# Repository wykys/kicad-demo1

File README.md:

# kicad-demo1
KiCAD demo1 project

[RS-12-L](https://www.tme.eu/en/Document/c23d5af46047cd50f4ab84101c968917/rs.pdf)

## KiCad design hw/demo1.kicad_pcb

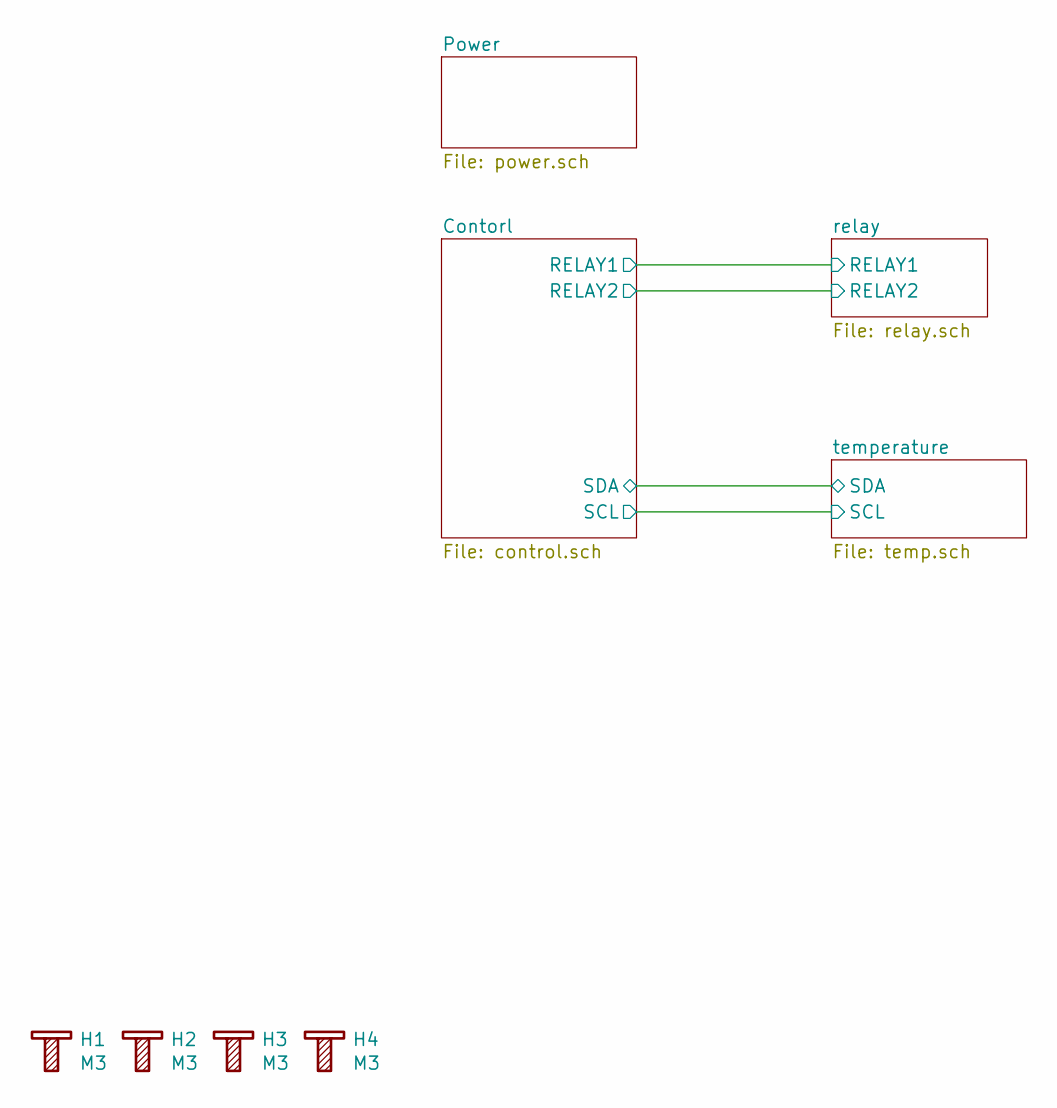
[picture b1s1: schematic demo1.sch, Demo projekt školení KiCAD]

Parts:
H1, H2, H3, H4: M3; Bolt_M3

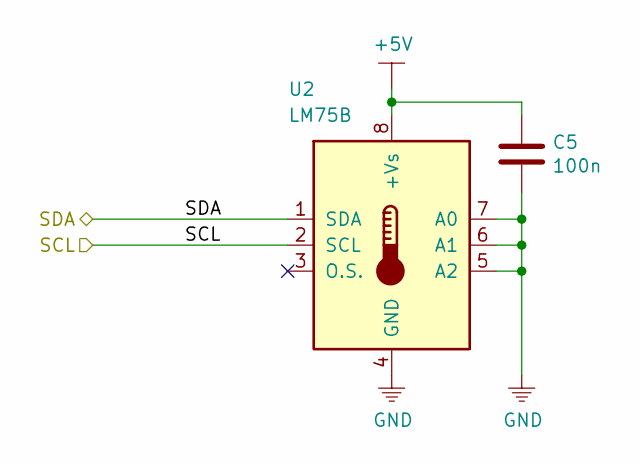
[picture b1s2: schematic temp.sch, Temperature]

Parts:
C5: 100n; C_0805_2012Metric
U2: LM75B; SOIC-8_3.9x4.9mm_P1.27mm

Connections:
+5V: C5.1, U2.8 (+Vs); also elsewhere on the board
/Contorl/SCL: U2.2 (SCL); also elsewhere on the board
/Contorl/SDA: U2.1 (SDA); also elsewhere on the board
GND: C5.2, U2.4 (GND), U2.5 (A2), U2.6 (A1), U2.7 (A0); also elsewhere on the board

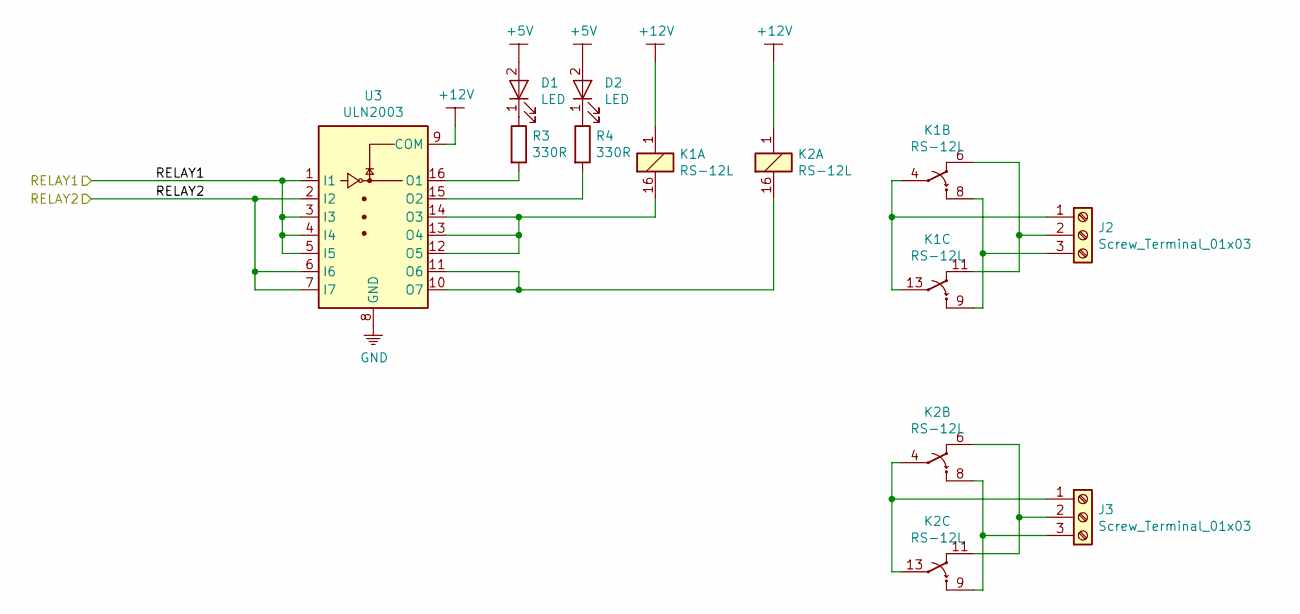
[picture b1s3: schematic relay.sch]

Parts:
D1, D2: LED; LED_0805_2012Metric
J2, J3: Screw_Terminal_01x03; PhoenixContact_MC_1,5_3-G-3.5_1x03_P3.50mm_Horizontal
K1, K2: RS-12L; RS-12-L
R3, R4: 330R; R_0805_2012Metric
U3: ULN2003; SOIC-16_3.9x9.9mm_P1.27mm

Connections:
+5V: D1.2 (A), D2.2 (A); also elsewhere on the board
+12V: K1.1, K2.1, U3.9 (COM); also elsewhere on the board
/Contorl/RELAY1: U3.1 (I1), U3.3 (I3), U3.4 (I4), U3.5 (I5); also elsewhere on the board
/Contorl/RELAY2: U3.2 (I2), U3.6 (I6), U3.7 (I7); also elsewhere on the board
GND: U3.8 (GND); also elsewhere on the board
unnamed: D1.1 (K), R3.1
unnamed: D2.1 (K), R4.1
unnamed: J2.1, K1.4, K1.13
unnamed: J2.2, K1.6, K1.11
unnamed: J2.3, K1.8, K1.9
unnamed: J3.1, K2.4, K2.13
unnamed: J3.2, K2.6, K2.11
unnamed: J3.3, K2.8, K2.9
unnamed: K1.16, U3.12 (O5), U3.13 (O4), U3.14 (O3)
unnamed: K2.16, U3.10 (O7), U3.11 (O6)
unnamed: R3.2, U3.16 (O1)
unnamed: R4.2, U3.15 (O2)

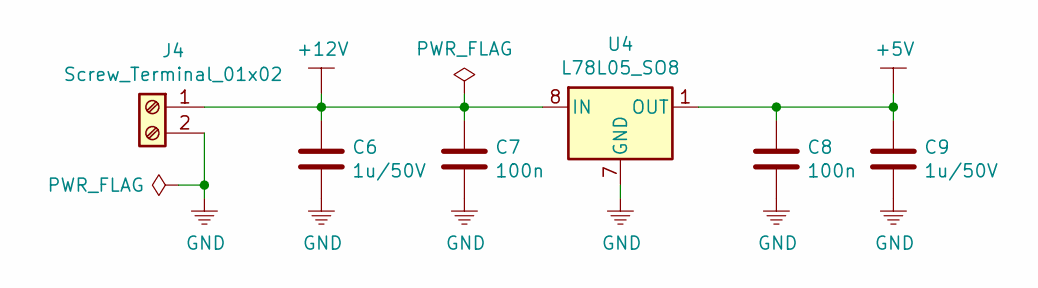
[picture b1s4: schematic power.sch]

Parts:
C6, C9: 1u/50V; C_0805_2012Metric
C7, C8: 100n; C_0805_2012Metric
J4: Screw_Terminal_01x02; PhoenixContact_MC_1,5_2-G-3.5_1x02_P3.50mm_Horizontal
U4: L78L05_SO8; SOIC-8_3.9x4.9mm_P1.27mm

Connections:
+5V: C8.1, C9.1, U4.1 (OUT); also elsewhere on the board
+12V: C6.1, C7.1, J4.1, U4.8 (IN); also elsewhere on the board
GND: C6.2, C7.2, C8.2, C9.2, J4.2, U4.2 (GND), U4.3 (GND), U4.6 (GND), U4.7 (GND); also elsewhere on the board

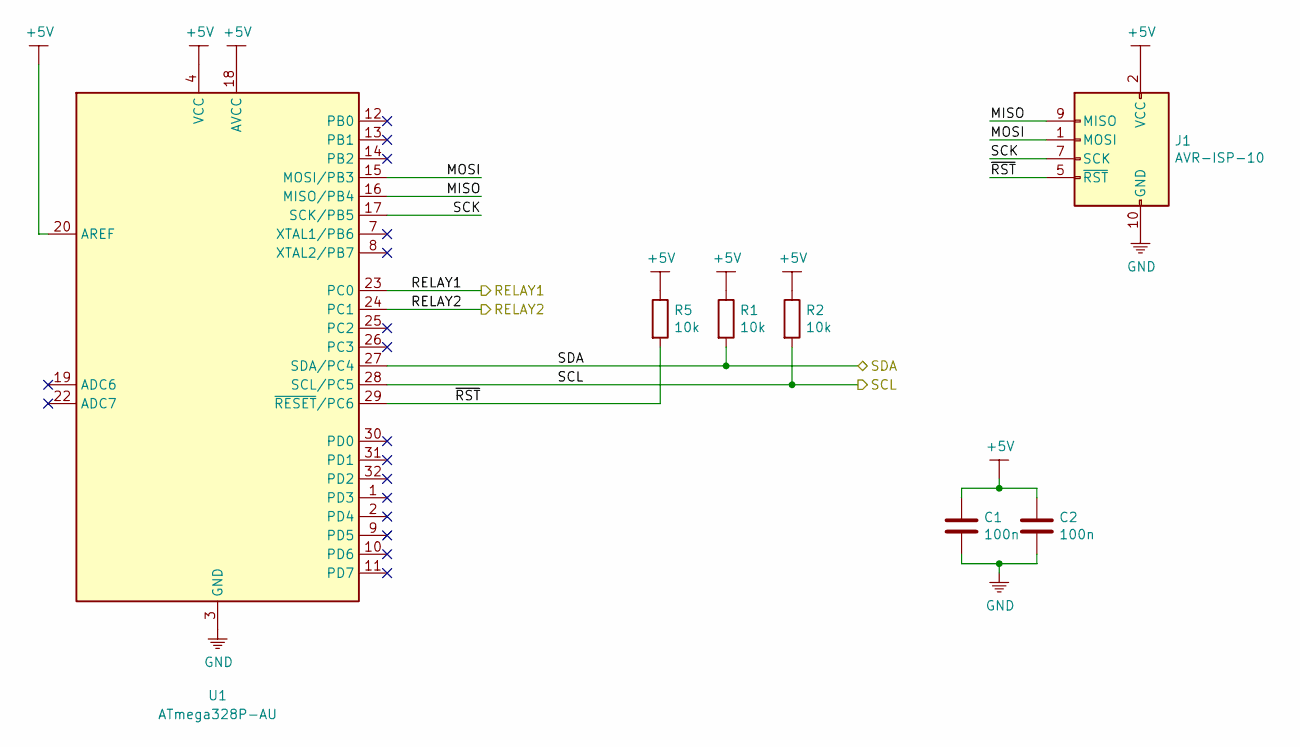
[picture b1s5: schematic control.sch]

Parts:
C1, C2: 100n; C_0805_2012Metric
J1: AVR-ISP-10; IDC-Header_2x05_P2.54mm_Vertical
R1, R2, R5: 10k; R_0805_2012Metric
U1: ATmega328P-AU; TQFP-32_7x7mm_P0.8mm

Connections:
+5V: C1.1, C2.1, J1.2 (VCC), R1.1, R2.1, R5.1, U1.4 (VCC), U1.6 (VCC), U1.18 (AVCC), U1.20 (AREF); also elsewhere on the board
/Contorl/MISO: J1.9 (MISO), U1.16 (MISO/PB4)
/Contorl/MOSI: J1.1 (MOSI), U1.15 (MOSI/PB3)
/Contorl/RELAY1: U1.23 (PC0); also elsewhere on the board
/Contorl/RELAY2: U1.24 (PC1); also elsewhere on the board
/Contorl/SCK: J1.7 (SCK), U1.17 (SCK/PB5)
/Contorl/SCL: R2.2, U1.28 (SCL/PC5); also elsewhere on the board
/Contorl/SDA: R1.2, U1.27 (SDA/PC4); also elsewhere on the board
/Contorl/~RST: J1.5 (~RST), R5.2, U1.29 (~RESET~/PC6)
GND: C1.2, C2.2, J1.4 (GND), J1.6 (GND), J1.8 (GND), J1.10 (GND), U1.3 (GND), U1.5 (GND), U1.21 (GND); also elsewhere on the board

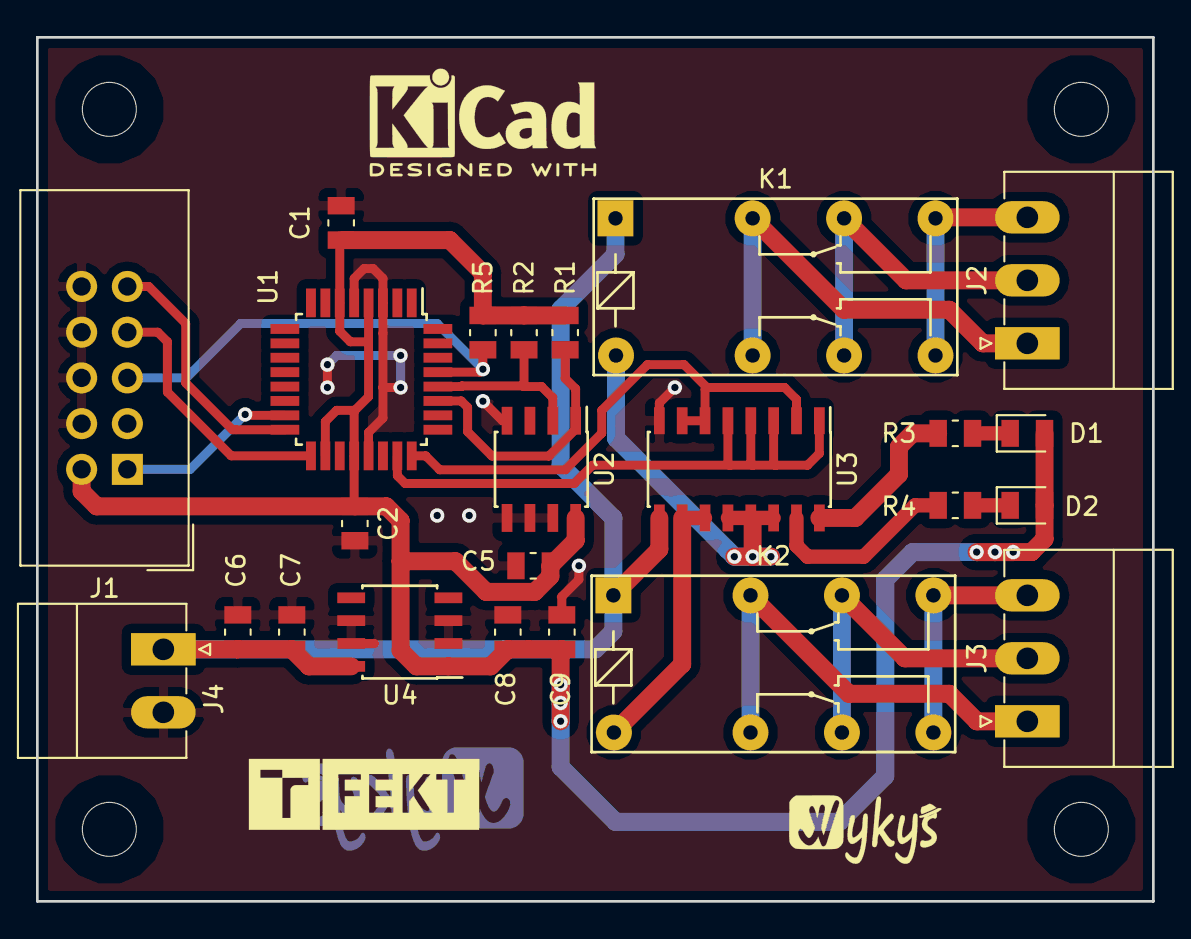
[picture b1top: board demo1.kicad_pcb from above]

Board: 2 copper layers, 62.0 x 48.0 mm, 28 parts (0 on the bottom side), 23 nets.

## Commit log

2018-04-05 added LICENSE
